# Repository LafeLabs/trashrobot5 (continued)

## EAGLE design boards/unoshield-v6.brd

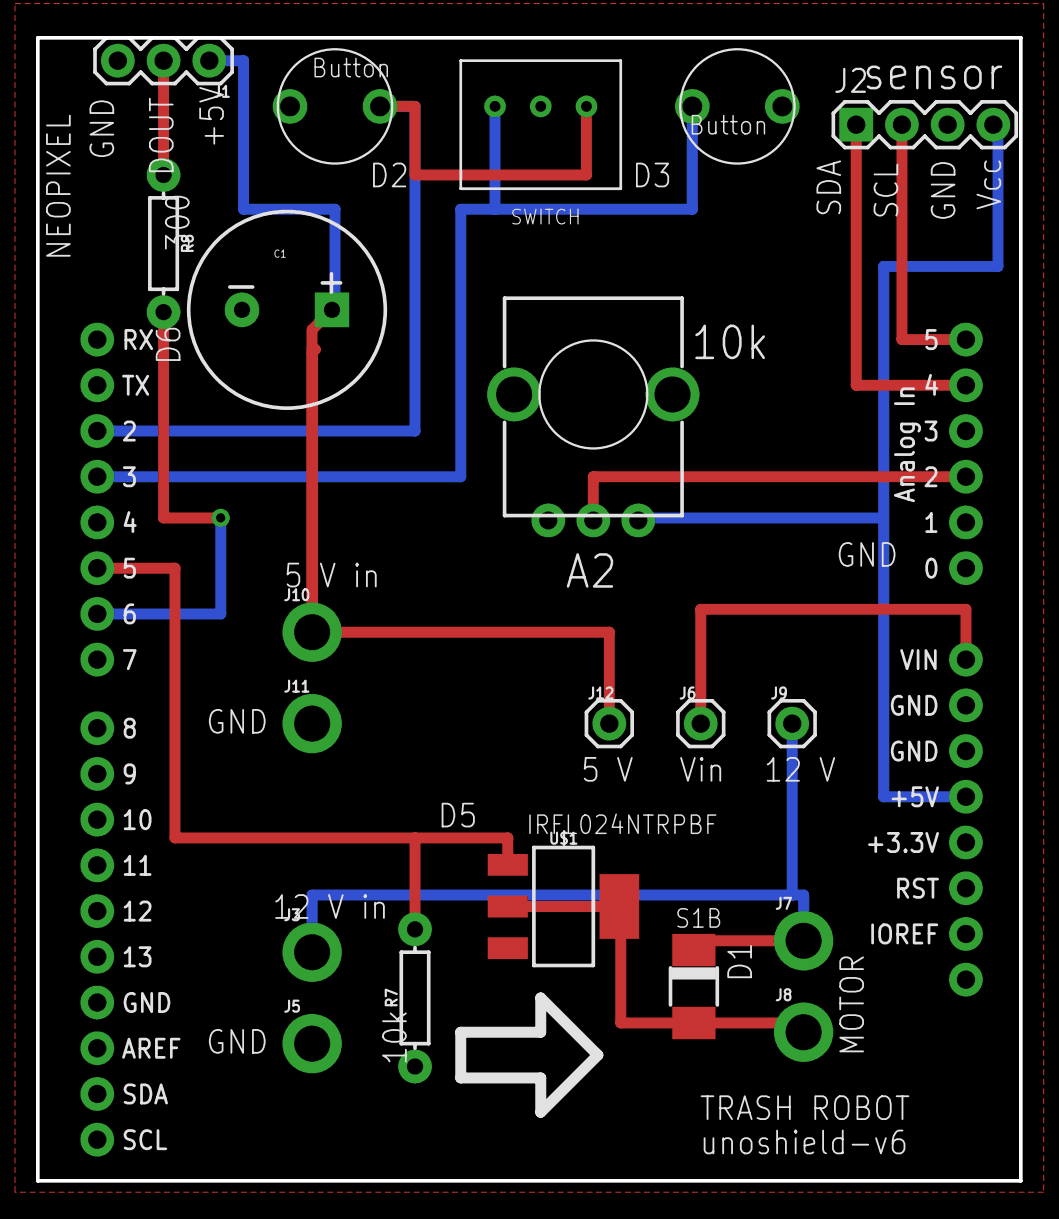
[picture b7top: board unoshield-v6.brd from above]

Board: 2 copper layers, 54.6 x 63.5 mm, 21 parts (0 on the bottom side), 14 nets.

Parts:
C1: 1000uf/25V; CPOL-RADIAL-1000UF-25V-KIT
D1: DO-214AC
J1: 455-1750-1-ND; 1X03
J2: 1X04
J3, J5, J7, J8, J10, J11: 1X01_2MM
J4: ARDUINO_R3_SHIELD; UNO_R3_SHIELD
J6, J9, J12: 1X01
R5: 20k; ALPS_POT_KIT
R7: 10k; AXIAL-0.3
R8: 300; AXIAL-0.3
SW1, SW2: BUTTON
SW3: ON-OFF-ON-360-1013-ND; 360-1013-ND
U$1: IRFL024NPBF; SOT223

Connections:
BUTTON: J4.D3, SW2.P$1, SW3.RIGHT
CL: J2.2, J4.A5
DA: J2.1, J4.A4
GND: C1.-, J1.3, J2.3, J4.GND@0, J4.GND@1, J4.GND@2, J5.1, J11.1, R5.P$1, R7.P$1, SW1.P$2, SW2.P$2, SW3.CENTER, U$1.3
unnamed: J4.D5, R7.P$2, U$1.1
unnamed: J4.D6, R8.P$2
unnamed: J4.VIN, J6.1
unnamed: C1.+, J1.1, J10.1, J12.1
unnamed: D1.A, J8.1, U$1.2, U$1.4
unnamed: J4.D2, SW1.P$1, SW3.LEFT
unnamed: J1.2, R8.P$1
unnamed: J4.A2, R5.P$2
VCC: J2.4, J4.5V, R5.P$3
VIN: D1.C, J3.1, J7.1, J9.1

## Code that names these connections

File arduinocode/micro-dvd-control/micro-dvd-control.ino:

int knob = 0;

int button1pin = 3;
int button2pin = 2;

int AIN1 = 7;
int AIN2 = 8;
int PWMA = 9;
int PWMB = 10;
int BIN1 = 11;
int BIN2 = 12;

boolean button1 = false;
boolean button2 = false;

int x = 0;

void setup() {
    pinMode(button1pin,INPUT_PULLUP); 
    pinMode(button2pin,INPUT_PULLUP); 
    pinMode(AIN1,OUTPUT);
    pinMode(AIN2,OUTPUT);
    pinMode(PWMA,OUTPUT);
    pinMode(BIN1,OUTPUT);
    pinMode(BIN2,OUTPUT);
    pinMode(PWMB,OUTPUT);
    
    analogWrite(PWMA,0);
    analogWrite(PWMB,0);
    digitalWrite(AIN1,LOW);
    digitalWrite(AIN2,LOW);
    digitalWrite(BIN1,LOW);
    digitalWrite(BIN2,LOW);

    knob = analogRead(A2);
    Serial.begin(9600);

}

void loop() {

  button1 = digitalRead(button1pin);  
  button2 = digitalRead(button2pin);  
  knob = analogRead(A2);
  if(knob < 512){
     x = 0.5*(512 - knob);
  }
  else{
     x = 0.5*(knob - 512);
  }
  Serial.println(x); 
  
  if(!button1 && button2){
      digitalWrite(BIN1,LOW);
      digitalWrite(BIN2,LOW);
      analogWrite(PWMB,0);
      if(knob < 512){
         digitalWrite(AIN2,LOW);
         digitalWrite(AIN1,HIGH);
      }
      else{
         digitalWrite(AIN1,LOW);
         digitalWrite(AIN2,HIGH);
      }
      analogWrite(PWMA,x);
  }  
  if(!button2 && button1){
      digitalWrite(AIN1,LOW);
      digitalWrite(AIN2,LOW);
      analogWrite(PWMA,0);
      if(knob < 512){
         digitalWrite(BIN2,LOW);
         digitalWrite(BIN1,HIGH);
      }
      else{
         digitalWrite(BIN1,LOW);
         digitalWrite(BIN2,HIGH);
      }
      analogWrite(PWMB,x);

  }
  if(button2 && button1){
      digitalWrite(AIN1,LOW);
      digitalWrite(AIN2,LOW);
      digitalWrite(BIN1,LOW);
      digitalWrite(BIN2,LOW);
      analogWrite(PWMA,0);
      analogWrite(PWMB,0);
     
  }
  if(!button2 && !button1){
      digitalWrite(AIN1,LOW);
      digitalWrite(AIN2,LOW);
      digitalWrite(BIN1,LOW);
      digitalWrite(BIN2,LOW);
      analogWrite(PWMA,0);
      analogWrite(PWMB,0);

  }


}

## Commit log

2019-11-13 trash robot 5 now has most recent versions of all files, is the official trash robot repository now
2019-11-13 files mostly ready to order now
2019-11-17 added readme with linked bom
2019-11-23 better links, localized dna and repilcatro
2019-11-30 added button stepper control
2019-12-07 more code
2020-04-28 more board desings, and arduino code
2020-04-29 pihat streamlined, largely laid out
2020-04-30 pihat v2 for pololu boards with potentiometers
2020-05-01 hat improvements, lots more arduino code
2020-05-01 small tweaks to pi hat
2020-11-19 added very useful arduino code
2020-11-19 git, like all things made by software scum, is horrible technology for horrible people. updated shield boards
2020-11-19 added some breakout plated holes for A0-A6 and power pins to button board
2020-12-08 xyz stepper control
2021-01-27 main program updates and new version of pcb updates
2021-01-31 better robot code, new board version
2021-01-31 C is an evil language for evil people :( but maybe memory problems are solved
2021-02-13 arduino
2021-02-18 smaller coin for default
2021-03-02 knob buttons code tweaks
2021-04-03 arduino bottle caps printer!!!
2021-08-21 added more neopixel programs
2022-02-02 uno shield board version 6
2022-02-07 updating library and version 6 shield
2022-02-07 shield tweaks
2022-02-08 gerbers zip made and submitted to pcbway
2022-02-08 saved screen shot of new board
2022-04-18 added controller code
2022-04-19 geometron coin printer with DVD drive micro z
2022-04-20 new arduino shield board with dual h bridge and 2 stepper drivers
2022-04-20 finishing touches on a draft of the full control board with slimezistor etc
2022-04-21 two new boards, xyz and slime and xyzhbridge and slime
